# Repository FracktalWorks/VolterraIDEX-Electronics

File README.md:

# VolterraIDEX-Electronics
Pin Configurations, EagleCAD and gerber files for Volterra IDEX PCBs

The following documentation contains the contents about the pin connections, firmware configurations of the BigTreeTech Octopus V1.1 which is assembled into the VolterraIDEX model of 400x400x370 buildsize.

## Initial Preparation
set jumpers as shown:

Green – Add Jumper

Red – Remove Jumper

1. Insert only the jumper in the Green and remove the other three jumpers in the Red in order to use TMC2209 UART mode.
2. Remove all the jumpers of DIAG to avoid the influence of TMC2209 DIAG on the endstop.
3. Remove the USB 5V power supply jumper to avoid the interaction between the USB 5V of raspberry pi and the DC-DC 5V of the motherboard.
4. Insert all the jumpers into V_FUSED to set the fan voltage to the system supply voltage.
5. Insert the jumper into V_FUSED to set the probe voltage to the system supply voltage.

## Wiring
1. Connect 24V and GND (V+ and V-) from the PSU to PWR and MOTOR_POWER
2. Connect the X(L) Motor (gantry left) to MOTOR0
3. Connect the X(R) Motor (gantry right) to MOTOR1 
4. Connect the E0 (Left Extruder front) motor to MOTOR2_1
5. Connect the E0' (Left Extruder back) motor to MOTOR2_2
6. Connect the Z motor to MOTOR3
7. Connect the Y (gantry left) to MOTOR4
8. Connect the Y1 (gantry right) to MOTOR5
9. Connect the E1 (Right Extruder front) to MOTOR6
10. Connect the E1' (Right Extruder back) to MOTOR7
11. Connect the Extruder0 hot end heater to HE0
12. Connect the Extruder1 hot end heater to HE1
13. Connect the bed SSR (DC Control Side) to HE2
14. Connect the Chamber SSR (DC Control Side) to HE3

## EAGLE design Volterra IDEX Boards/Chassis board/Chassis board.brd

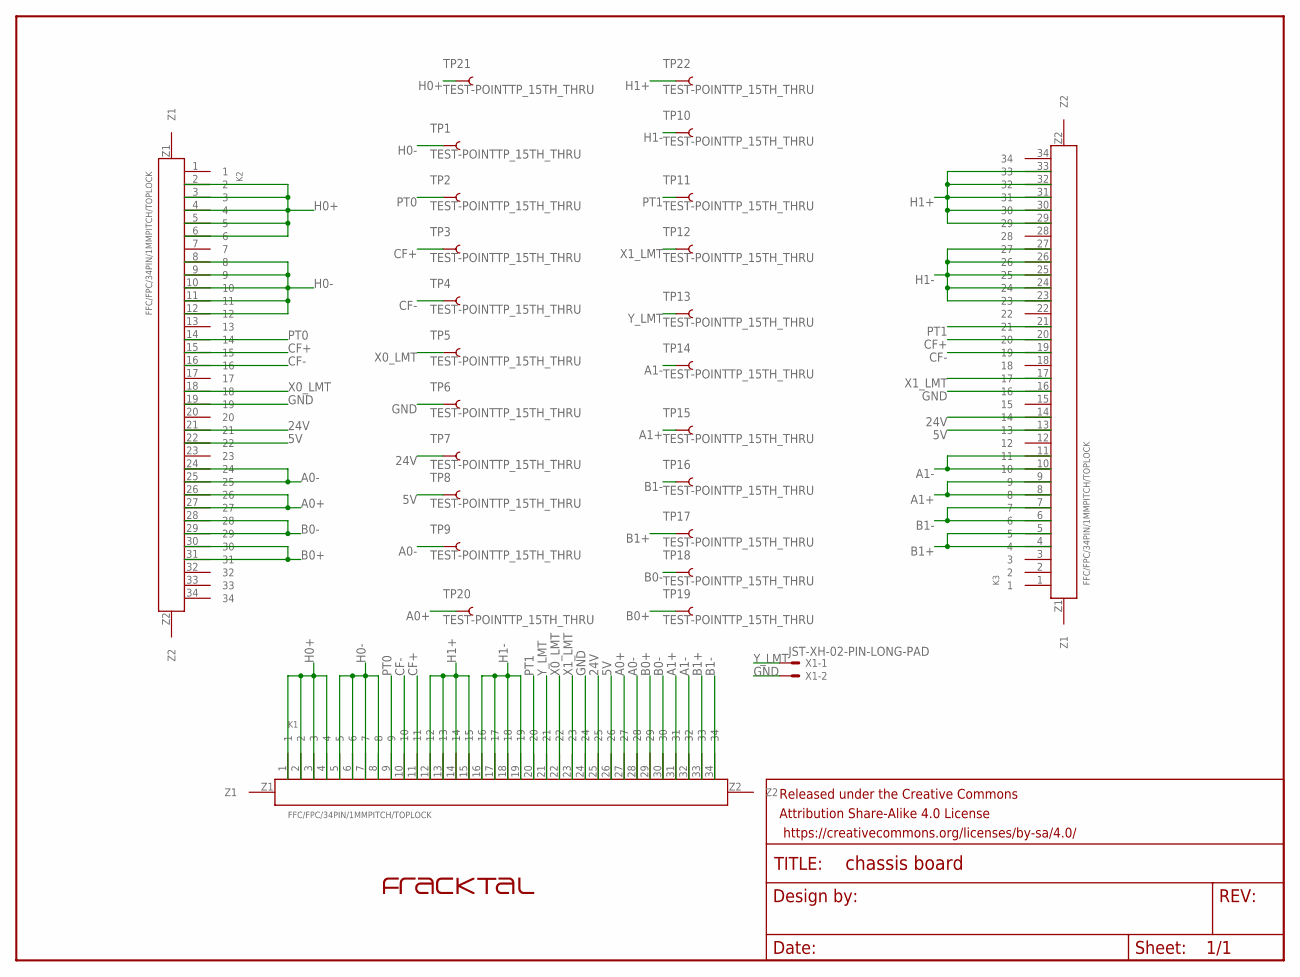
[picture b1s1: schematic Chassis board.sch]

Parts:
FRAME1: FRAME-LETTER; CREATIVE_COMMONS
K1, K2, K3: FFC/FPC/34PIN/1MMPITCH/TOPLOCK; 34PIN/1MMPITCH/FFC/FPC
TP1, TP2, TP3, TP4, TP5, TP6, TP7, TP8, TP9, TP10, TP11, TP12, TP13, TP14, TP15, TP16, TP17, TP18, TP19, TP20, TP21, TP22: TEST-POINTTP_15TH_THRU; TP_15TH
U$2: FRACKTALLOGO
X1: JST-XH-02-PIN-LONG-PAD; JST-XH-02-PACKAGE-LONG-PAD

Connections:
5V: K1.26, K2.22, K3.13, TP8.P$1
24V: K1.25, K2.21, K3.14, TP7.P$1
A0+: K1.27, K2.26, K2.27, TP20.P$1
A0-: K1.28, K2.24, K2.25, TP9.P$1
A1+: K1.31, K3.8, K3.9, TP15.P$1
A1-: K1.32, K3.10, K3.11, TP14.P$1
B0+: K1.29, K2.30, K2.31, TP19.P$1
B0-: K1.30, K2.28, K2.29, TP18.P$1
B1+: K1.33, K3.4, K3.5, TP17.P$1
B1-: K1.34, K3.6, K3.7, TP16.P$1
CF+: K1.11, K2.15, K3.20, TP3.P$1
CF-: K1.10, K2.16, K3.19, TP4.P$1
GND: K1.24, K2.19, K3.16, TP6.P$1, X1.2
H0+: K1.1, K1.2, K1.3, K1.4, K2.2, K2.3, K2.4, K2.5, K2.6, TP21.P$1
H0-: K1.5, K1.6, K1.7, K1.8, K2.8, K2.9, K2.10, K2.11, K2.12, TP1.P$1
H1+: K1.12, K1.13, K1.14, K1.15, K3.29, K3.30, K3.31, K3.32, K3.33, TP22.P$1
H1-: K1.16, K1.17, K1.18, K1.19, K3.23, K3.24, K3.25, K3.26, K3.27, TP10.P$1
PT0: K1.9, K2.14, TP2.P$1
PT1: K1.20, K3.21, TP11.P$1
X0_LMT: K1.22, K2.18, TP5.P$1
X1_LMT: K1.23, K3.17, TP12.P$1
Y_LMT: K1.21, TP13.P$1, X1.1

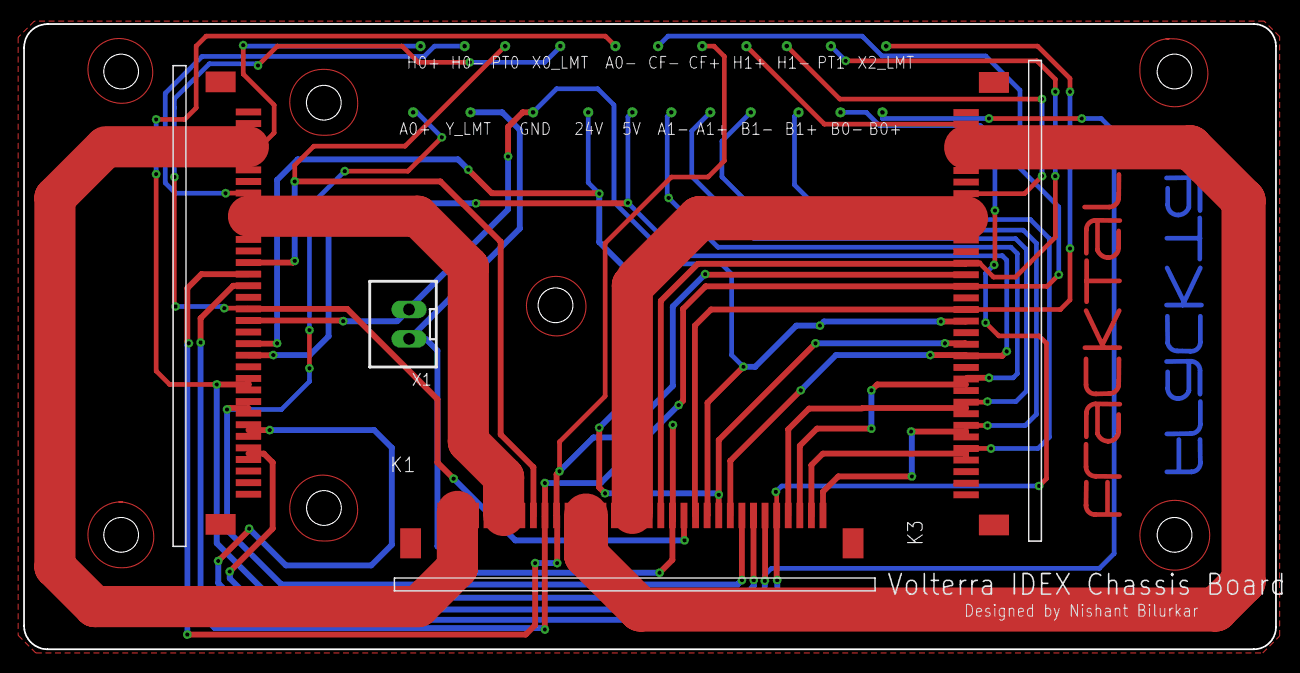
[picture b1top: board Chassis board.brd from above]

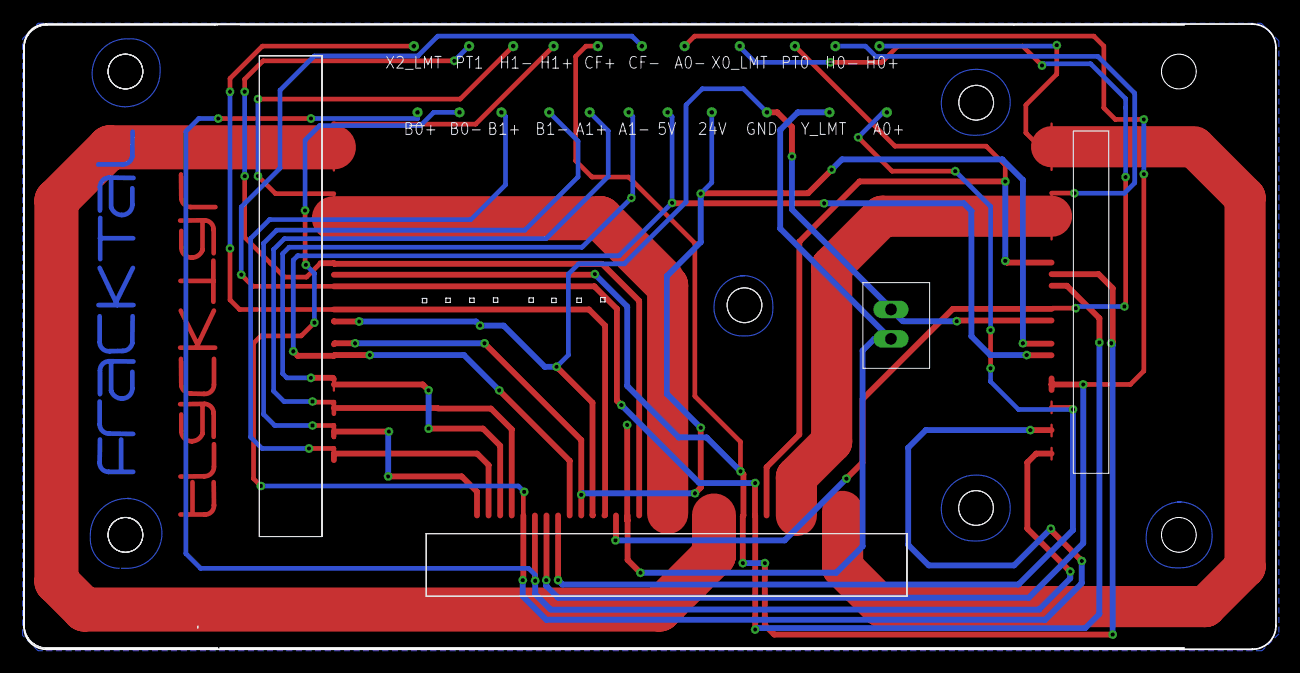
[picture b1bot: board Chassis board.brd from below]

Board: 2 copper layers, 108.1 x 54.0 mm, 29 parts (23 on the bottom side), 22 nets.

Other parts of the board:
U$3: FRACKTALLOGO

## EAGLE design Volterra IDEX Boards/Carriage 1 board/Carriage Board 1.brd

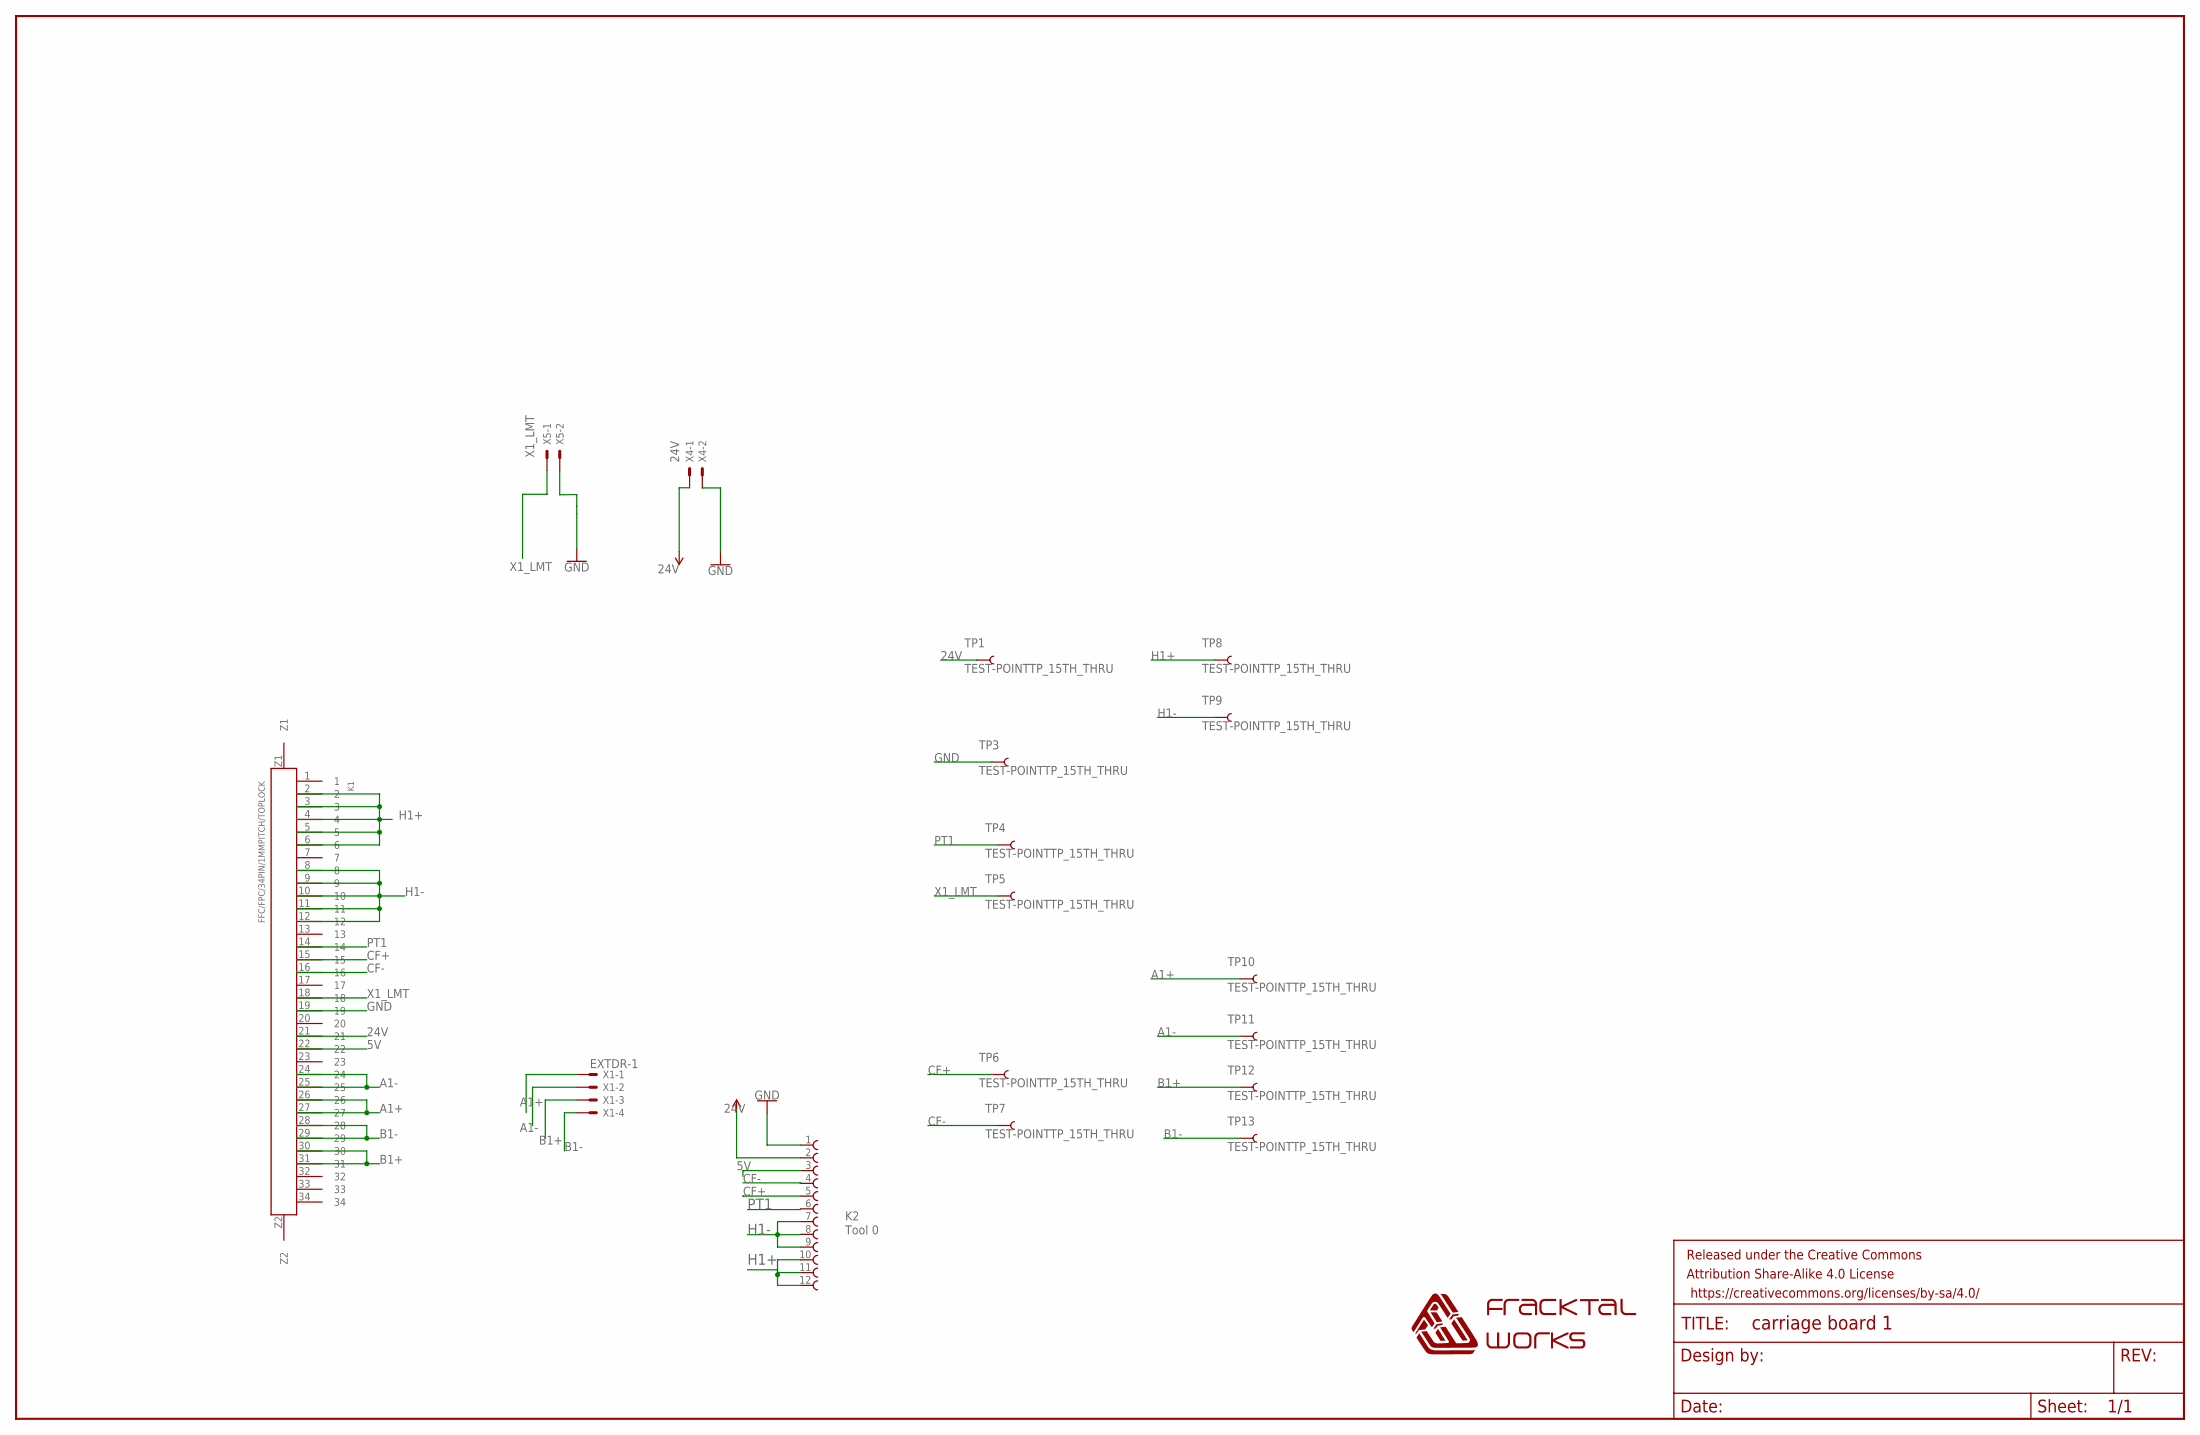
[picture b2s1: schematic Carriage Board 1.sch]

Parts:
FRAME1: FRAME-LEDGER; CREATIVE_COMMONS
K1: FFC/FPC/34PIN/1MMPITCH/TOPLOCK; 34PIN/1MMPITCH/FFC/FPC
K2: Tool 0; 68611214122
TP1, TP3, TP4, TP5, TP6, TP7, TP8, TP9, TP10, TP11, TP12, TP13: TEST-POINTTP_15TH_THRU; TP_15TH
U$2: FWLOGO
X1: EXTDR-0; JST-XH-04-PACKAGE-LONG-PAD
X4: 24V; JST-XH-02-PACKAGE-LONG-PAD
X5: X_LMT; JST-XH-02-PACKAGE-LONG-PAD

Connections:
5V: K1.22, K2.3
24V: K1.21, K2.2, TP1.P$1, X4.1
A1+: K1.26, K1.27, TP10.P$1, X1.1
A1-: K1.24, K1.25, TP11.P$1, X1.2
B1+: K1.30, K1.31, TP12.P$1, X1.3
B1-: K1.28, K1.29, TP13.P$1, X1.4
CF+: K1.15, K2.5, TP6.P$1
CF-: K1.16, K2.4, TP7.P$1
GND: K1.19, K2.1, TP3.P$1, X4.2, X5.2
H1+: K1.2, K1.3, K1.4, K1.5, K1.6, K2.10, K2.11, K2.12, TP8.P$1
H1-: K1.8, K1.9, K1.10, K1.11, K1.12, K2.7, K2.8, K2.9, TP9.P$1
PT1: K1.14, K2.6, TP4.P$1
X1_LMT: K1.18, TP5.P$1, X5.1

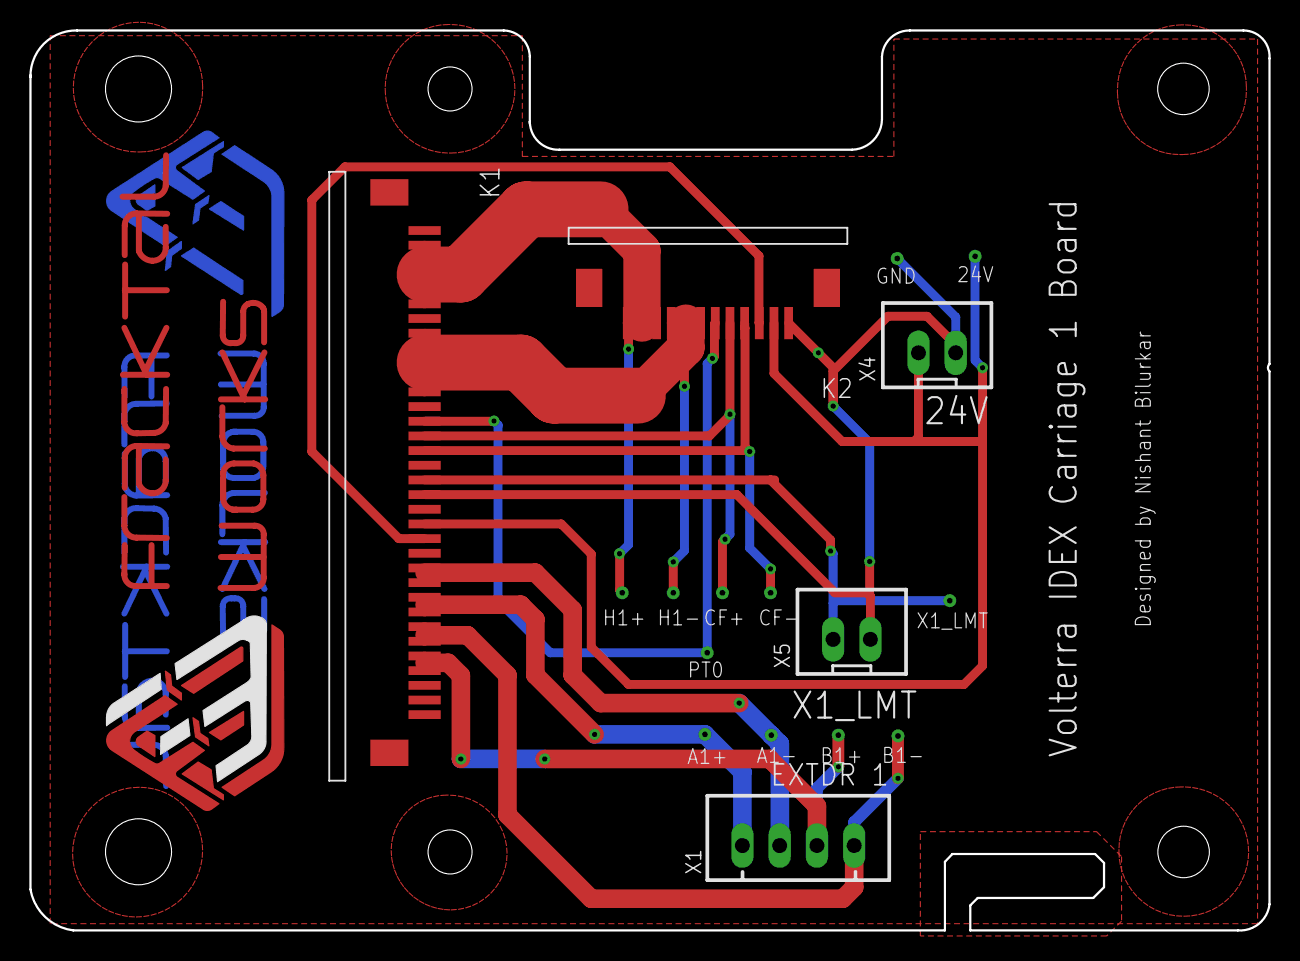
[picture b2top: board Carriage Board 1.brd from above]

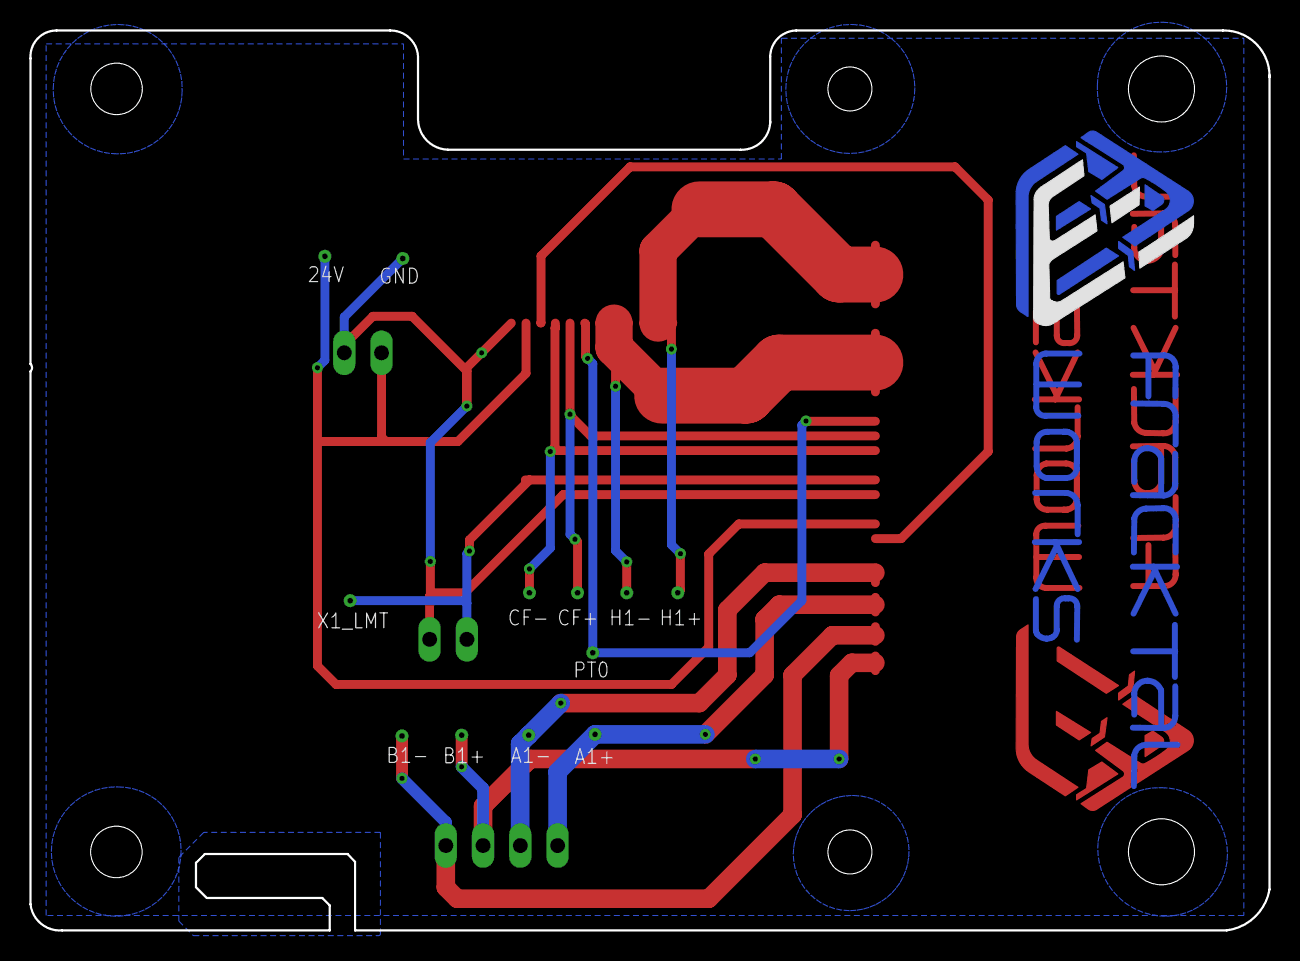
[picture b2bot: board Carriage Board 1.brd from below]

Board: 2 copper layers, 84.5 x 61.3 mm, 20 parts (12 on the bottom side), 13 nets.

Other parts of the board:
U$1: FWLOGO

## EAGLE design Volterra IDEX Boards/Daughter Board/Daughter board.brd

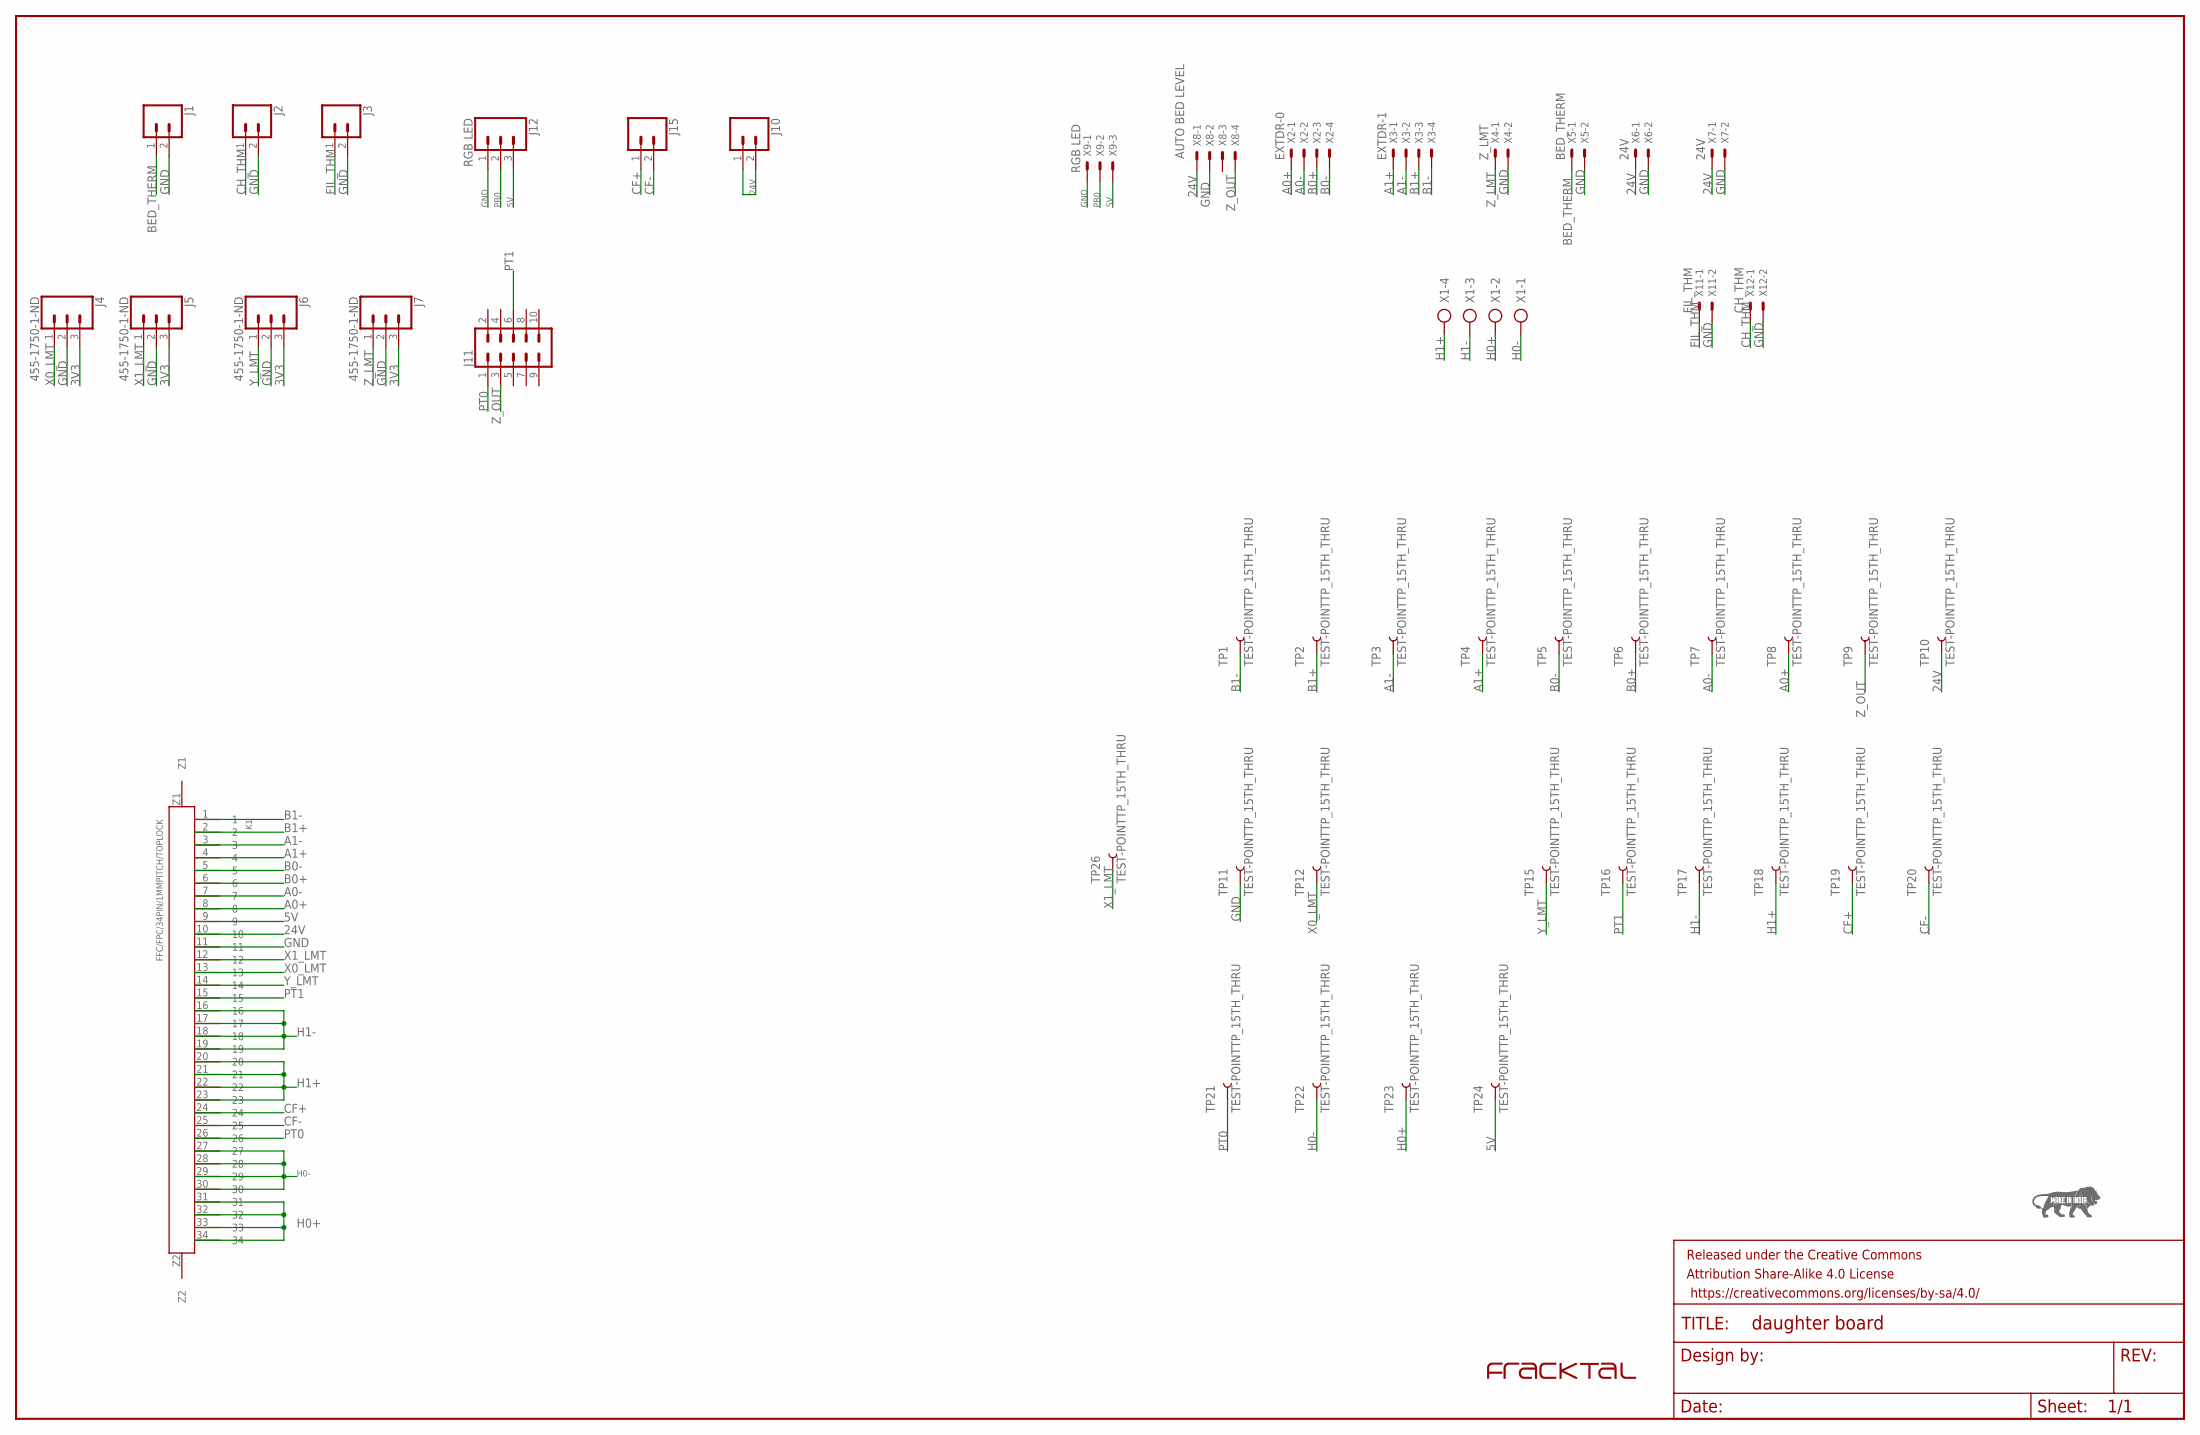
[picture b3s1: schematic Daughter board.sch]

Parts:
FRAME1: FRAME-LEDGER; CREATIVE_COMMONS
J1, J2, J3, J10, J15: CONN_02; 1X02
J4, J5, J6, J7: 455-1750-1-ND; 1X03
J11: CONN_05X2NO_SILK; 2X5_NOSILK
J12: RGB LED; 1X03
K1: FFC/FPC/34PIN/1MMPITCH/TOPLOCK; 34PIN/1MMPITCH/FFC/FPC
TP1, TP2, TP3, TP4, TP5, TP6, TP7, TP8, TP9, TP10, TP11, TP12, TP15, TP16, TP17, TP18, TP19, TP20, TP21, TP22, TP23, TP24, TP26: TEST-POINTTP_15TH_THRU; TP_15TH
U$1: FRACKTALLOGO
U$2: MAKEININDIA
X1: AK500/4
X2: EXTDR-0; JST-XH-04-PACKAGE-LONG-PAD
X3: EXTDR-1; JST-XH-04-PACKAGE-LONG-PAD
X4: Z_LMT; JST-XH-02-PACKAGE-LONG-PAD
X5: BED_THERM; JST-XH-02-PACKAGE-LONG-PAD
X6, X7: 24V; JST-XH-02-PACKAGE-LONG-PAD
X8: AUTO BED LEVELING; JST-XH-04-PACKAGE-LONG-PAD
X9: RGB LED; JST-XH-03-PACKAGE-LONG-PAD
X11: FIL_THM; JST-XH-02-PACKAGE-LONG-PAD
X12: CH_THM; JST-XH-02-PACKAGE-LONG-PAD

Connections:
3V3: J4.3, J5.3, J6.3, J7.3
5V: J12.3, K1.9, TP24.P$1, X9.3
24V: J10.1, J10.2, K1.10, TP10.P$1, X6.1, X7.1, X8.1
A0+: K1.8, TP8.P$1, X2.1
A0-: K1.7, TP7.P$1, X2.2
A1+: K1.4, TP4.P$1, X3.1
A1-: K1.3, TP3.P$1, X3.2
B0+: K1.6, TP6.P$1, X2.3
B0-: K1.5, TP5.P$1, X2.4
B1+: K1.2, TP2.P$1, X3.3
B1-: K1.1, TP1.P$1, X3.4
BED_THERM: J1.1, X5.1
CF+: J15.1, K1.24, TP19.P$1
CF-: J15.2, K1.25, TP20.P$1
CH_THM: J2.1, X12.1
FIL_THM: J3.1, X11.1
GND: J1.2, J2.2, J3.2, J4.2, J5.2, J6.2, J7.2, J12.1, K1.11, TP11.P$1, X4.2, X5.2, X6.2, X7.2, X8.2, X9.1, X11.2, X12.2
H0+: K1.31, K1.32, K1.33, K1.34, TP23.P$1, X1.2
H0-: K1.27, K1.28, K1.29, K1.30, TP22.P$1, X1.1
H1+: K1.20, K1.21, K1.22, K1.23, TP18.P$1, X1.4
H1-: K1.16, K1.17, K1.18, K1.19, TP17.P$1, X1.3
PB0: J12.2, X9.2
PT0: J11.1, K1.26, TP21.P$1
PT1: J11.6, K1.15, TP16.P$1
X0_LMT: J4.1, K1.13, TP12.P$1
X1_LMT: J5.1, K1.12, TP26.P$1
Y_LMT: J6.1, K1.14, TP15.P$1
Z_LMT: J7.1, X4.1
Z_OUT: J11.3, TP9.P$1, X8.4

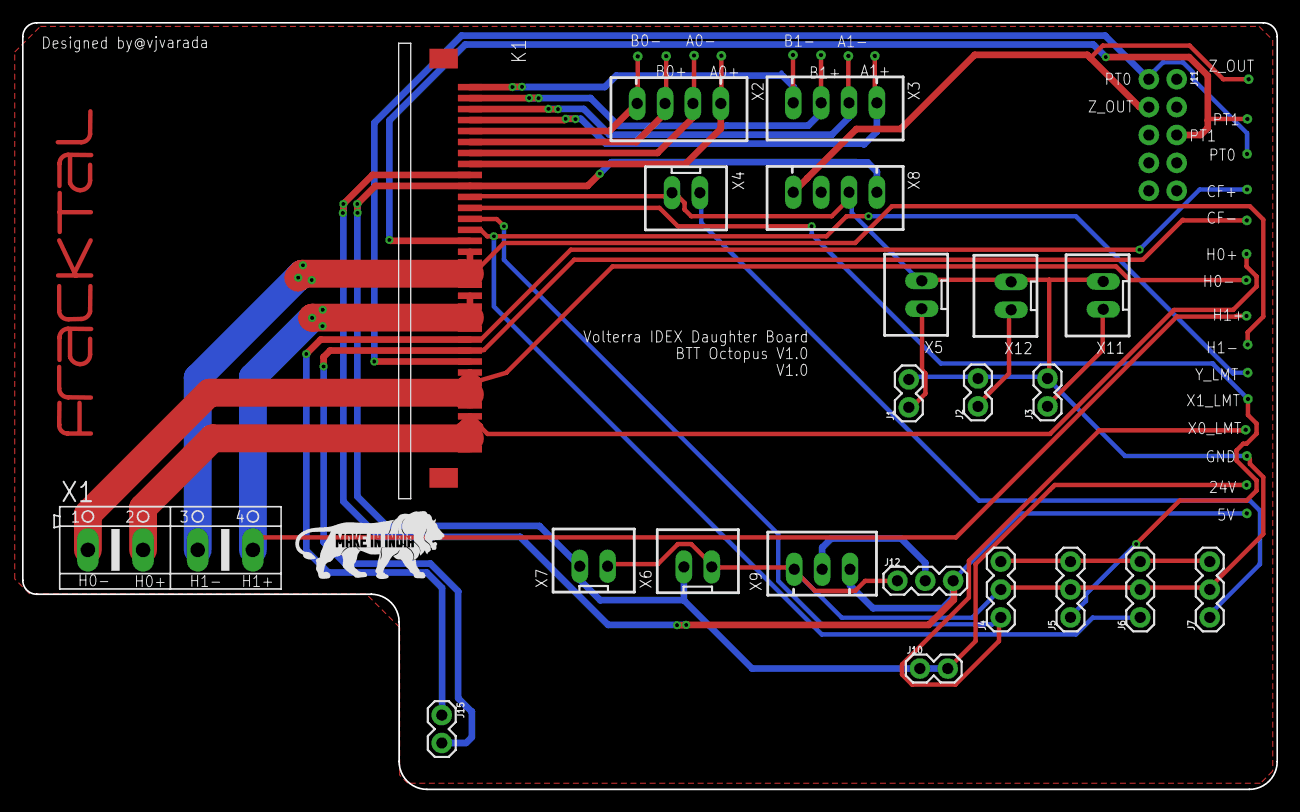
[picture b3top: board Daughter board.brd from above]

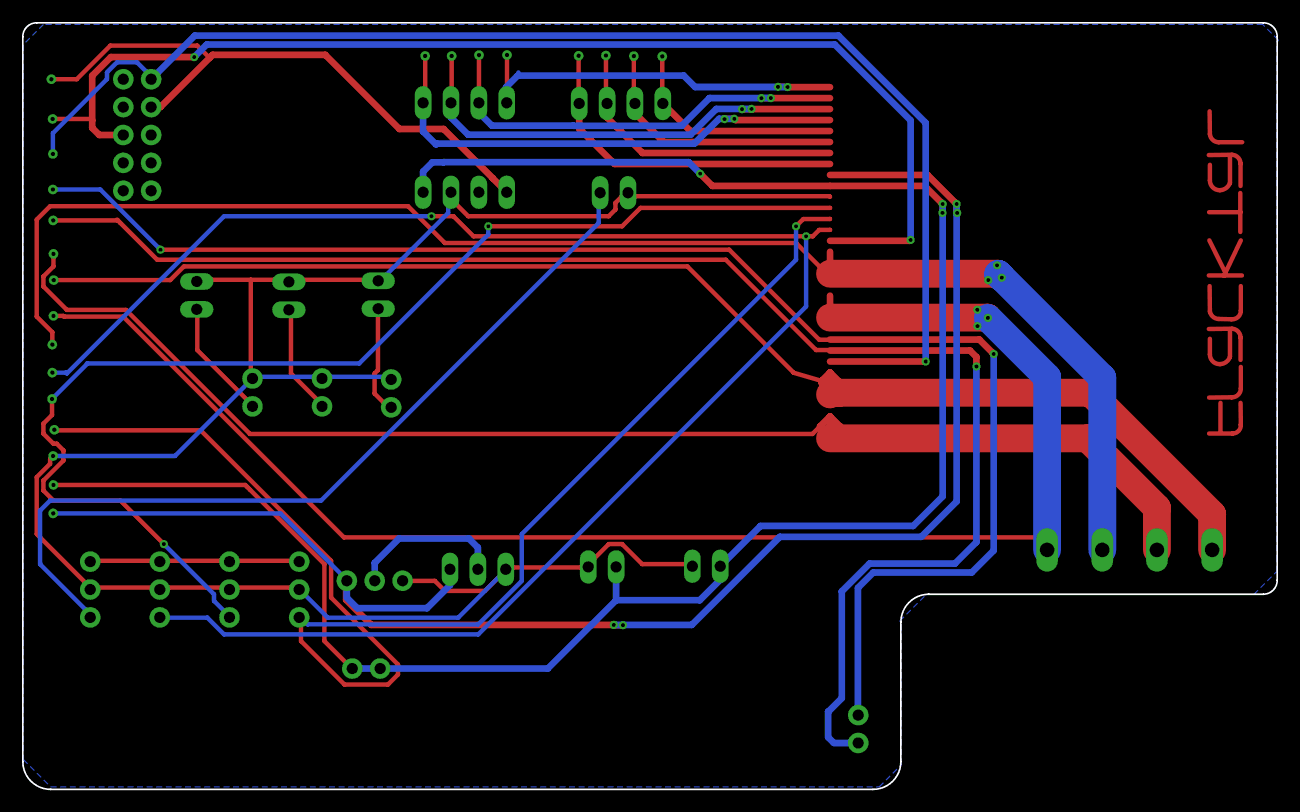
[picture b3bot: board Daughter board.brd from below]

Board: 2 copper layers, 114.3 x 69.8 mm, 49 parts (23 on the bottom side), 29 nets.

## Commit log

2023-01-11 Volterra IDEX PCB files
    Uploaded Chassis, Carriage 0 and Carriage 1 boards
2023-01-12 Daughter board added
2023-01-12 DRC added
2023-01-12 Switching of carriage board numbering, changing extruder FFC pins and fixing routings
2023-01-12 Updated Daughter board schematic and other boards
2023-01-12 DRC checked of Chassis, Carriage 1 & 2, and created CAM files
2023-01-13 Added Daughter Board
2023-01-13 Board files added
2023-01-13 Updated Chassis, Carriage 0 and 1 CAM and gerber files
2023-02-06 Updated Chassis Board mount holes and re-routing
2023-03-18 Volterra IDEX Electronics Documentation
2023-04-04 Attached manual

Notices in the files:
parts and their libraries:
SparkFun-Aesthetics: Licensing: Creative Commons ShareAlike 4.0 International - https://creativecommons.org/licenses/by-sa/4.0
SparkFun-Aesthetics: Released under the Creative Commons Attribution Share-Alike 4.0 License
SparkFun-Aesthetics: https://creativecommons.org/licenses/by-sa/4.0
